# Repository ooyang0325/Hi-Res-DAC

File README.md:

# Hi-Res DAC + balanced headphone amplifier

The current layout review candidate is the editable [120 × 100 mm integrated-audio KiCad board](hardware/DAC_HPA_120x100_INTEGRATED_AUDIO_STUDY_ONLY.kicad_pcb), with manual placement and partial routing, paired with the [schematic](hardware/DAC_HPA.kicad_sch). Parts List v0.9 and Calculation Package v1.1 remain the baseline; the [captured ECO](hardware/FUNCTIONAL_ECO_2026-09-28.md) adds buffered supervisor readbacks and local J702 TVS parts. The incoming layout engineer should start with the [29 September handoff](hardware/LAYOUT_ENGINEER_HANDOFF_2026-09-29.md); peer reviewers can use the [reviewer guide](hardware/REVIEWER_START_HERE.md). The full-rate MCU capture guard, physical overlays, output routability and JLCPCB process gates remain open. No PCB manufacturing or PCBA order files are released.

## GitLab CI/CD

`.gitlab-ci.yml` uses the fixed official KiCad 10.0.1 container. Every pipeline checks schematic regeneration, netlist/ERC, the exact ECO delta, attach-charge arithmetic, placement geometry, JLC fabrication/assembly proxies, DRC and 3D model paths. A successful pipeline delivers the nine-page review PDF, the integrated-audio board's 3D GLB and top/L2/L3/bottom SVGs, earlier board GLBs for comparison, reviewer guides, BOM CSVs and a ZIP of the committed source as downloadable artifacts for 30 days.

The GitLab review package is **not** a manufacturing release. The connector and physical gates are tracked in [connector review](hardware/CONNECTOR_REVIEW.md) and [PCBA process review](hardware/PCBA_PROCESS_REVIEW.md). A routed PCB and CPL would be required for a PCBA upload.

The latest [DAC/core checkpoint](hardware/DAC_CORE_ROUTE_STUDY.md) records BCLK/LRCLK/SDATA at 22.213/22.324/22.879 mm and MCLK at 8.381 mm. The current integrated board has 544 footprints, 250 nets, 855 track/via items (143 vias), 864 full ratsnest links, 499 DRC-unconnected items and zero DRC violations. Its manual delta is 138 moves, eight source-copper removals and 828 additions. C622 has local 3V3D and GND copper; the global 3V3D feed remains open. All 12 U609/U610 timer branches pass the ≤8 mm screen without timer-net vias; C635/C636 U609 bypasses are locally connected, while upstream rail feeds and U609 VT/control escapes remain open. The [integrated-audio route study](hardware/INTEGRATED_AUDIO_ROUTE_STUDY.md) covers the DAC/I/V, amplifier-input, U501 and amplifier-to-jack copper including the completed U609/U610 timer branches and U609 local bypass work. Two U202 and five U301 exposed-pad vias are filled and capped; U401/U402 output-amplifier EP thermal routes remain open. The [via-pad audit](hardware/INTEGRATED_AUDIO_VIA_PAD_PROCESS_AUDIT.json) still flags 45 unfilled via-to-SMT-pad sites within 0.35 mm for JLC mask/process review. Full routing, system ESD, EMI and audio tests remain open; zero DRC violations apply to partial copper only.

The [schematic simplification review](hardware/SCHEMATIC_SIMPLIFICATION_REVIEW.md) lists three small DNF options for later review. Both headphone jacks and USB High mode remain required. The [discharge capture review](hardware/DISCHARGE_CAPTURE_REVIEW.md) identifies an open U303 calculation mismatch and links a separate [three-resistor 2512 fit option](hardware/DAC_HPA_120x100_DISCHARGE_FIT_OPTION_ONLY.kicad_pcb); the captured EN connection remains intentional, and the option is not a schematic/BOM change. The [Freerouting probe](hardware/FREEROUTING_PROBE.md) rejected a whole-board route and records two individually reviewed low-speed paths adopted later. The [functional-ECO board](hardware/DAC_HPA_120x100_FUNCTIONAL_ECO_STUDY_ONLY.kicad_pcb) is the preceding placement baseline; the former primary and [macro study](hardware/MACRO_PLACEMENT_REVIEW.md) are earlier comparisons. No PCBA order is authorized.

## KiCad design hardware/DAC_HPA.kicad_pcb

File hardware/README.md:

# DAC-HPA KiCad schematic and routing studies

**Sending this design for peer review?** Begin with the [layout handover report](LAYOUT_HANDOVER_REPORT.md) and [REVIEWER_START_HERE.md](REVIEWER_START_HERE.md), then use the [schematic](SCHEMATIC_REVIEW_GUIDE.md), [placement](PLACEMENT_REVIEW_GUIDE.md), and [command-line visual inspection](PCB_CLI_VISUAL_REVIEW.md) guides. The [findings template](REVIEW_FINDINGS_TEMPLATE.md) records actionable review results against one Git commit.

The [functional-ECO placement baseline](DAC_HPA_120x100_FUNCTIONAL_ECO_STUDY_ONLY.kicad_pcb) is a separate 120 × 100 mm review board made from explicit hand-selected coordinates. It includes the [readback, J702 TVS and I/V A/B-channel schematic ECO](FUNCTIONAL_ECO_2026-09-28.md), a tighter DAC bypass row and the local J702 TVS branches. The [integrated audio study](INTEGRATED_AUDIO_ROUTE_STUDY.md) is the current routing review candidate; the newer [DAC/core checkpoint](DAC_CORE_ROUTE_STUDY.md) records its latest clock, I²S and local power routes. The [Freerouting probe](FREEROUTING_PROBE.md) rejects the whole-board result and documents two selectively adopted low-speed routes. [Layout review](FUNCTIONAL_ECO_LAYOUT_REVIEW.md) and [constraint disposition](CONSTRAINT_DISPOSITION_V2.md) state the remaining route work. `DAC_HPA.kicad_pcb` and the [prior macro study](MACRO_PLACEMENT_REVIEW.md) are historical comparisons; they predate the eight added parts.

Open `DAC_HPA.kicad_pro` or `DAC_HPA.kicad_sch` in KiCad 10. The root page links eight circuit sheets following Design Spec v1.1, Schematic Design Notes v1.0, Parts List v0.9, and Capture Update Note v1.0.

`DAC_HPA_review_only.pdf` is a nine-page visual export of the current provisional capture. The expanded protection sheet uses A1; smaller blocks use A2/A3/A4. Each sheet title block identifies v1.1-ECO1 and the open F01/F03/G-1–G-4 holds. The KiCad project is the editable source.

## Current status

- The v0.9 workbook has 526 netlisted designators and 1,445 pin rows; those rows still match Calculation Package v1.1. The [asserted functional ECO](FUNCTIONAL_ECO_2026-09-28.md) adds eight parts and reassigns equivalent U403/U404 A/B channels to match the manual I/V macro. KiCad now has **534 netlisted designators, 1,465 pins, 1,422 connected pins, 43 no-connect pins and 250 named nets**, plus four grounded mounting holes and seven fiducials. The exact **34** workbook-to-capture pin/net differences are checked; they include the earlier D705/D706 polarity fix. J702 pins 5/6 remain no-connect break contacts.
- Per-part MPN, LCSC code, fit class, package, and rating/tolerance properties are included for later [JLCPCB BOM preparation](https://jlcpcb.com/help/article/how-to-generate-the-bom-and-centroid-file-from-kicad). The owner approved changing U403/U404 from workbook OPA2210IDR SOIC-8 to OPA2210IDGKR VSSOP-8, C2876414. `generate_schematic.py` asserts the old workbook entry and applies this explicit override; `IV_7MM_RECHECK.md` records the provisional 7 mm input-route reassessment and sourcing/footprint limitations.
- The review-only JLCPCB BOM contains **463 placed parts**, seven owner-fitted and nine DNF parts. Fourteen placed parts have no LCSC code and need the documented global-sourcing process. The three CSVs are **not** an order package; a routed PCB and CPL are still required.
- The schematic-aligned four-layer **120 × 100 mm functional-ECO baseline** has **544 footprints and 250 named nets**; J703 remains a schematic DNF option with no PCB pads. Its partial copper comprises J701/J702 local TVS branches and the hand-routed X201→R203→U301 MCLK trunk, R227 return and R665→U607 monitor input: **28 F.Cu tracks, seven vias** and one filled L2 GND zone. It has zero geometry DRC violations and 1,144 full ratsnest gaps. The old 536-footprint primary and 100 × 80/100 × 100 mm boards are historical comparisons.
- The [separate 270° output-macro study](OUTPUT_MACRO_ROUTE_STUDY.md) keeps the same schematic/pad map and manually connects all four U401/U402 amplifier outputs and local feedback to K601–K604 relay inputs. Its partial copper passes custom-rule DRC, but the jack outputs, input/T networks, supply returns and L3/L4 audio return remain on hold; it is a comparison, not the primary order board.
- The current [integrated-audio routing study](INTEGRATED_AUDIO_ROUTE_STUDY.md) routes four DAC→I/V inputs, eight I/V→first-T feeds, all eight local input T triplets and all four amplifier-to-jack paths. The current board has **855 track/via items (143 vias), zero DRC violations, 499 DRC-reported unconnected items and 864 full `pcbnew` ratsnest links**. Its manual record has **138 footprint moves, eight removed source-copper items and 828 added items**. DACL/DACLB/DACR/DACRB no-via F.Cu routes measure **4.294/6.030/6.837/4.786 mm** against the provisional 7 mm target, leaving DACR **0.163 mm**. Saved L2 GND is directly below all four input traces at 0.01 mm route samples and offsets 0, ±0.05, ±0.10 mm. The longest I/V→first-T feed is **47.752 mm** on the right; the largest projected 2D I/V feedback area is **4.875 mm²**, excluding vertical and return-current area. DACL's U403→C417 feedback branch still lacks direct L2 for **1.9426 mm** of centreline (**+0.0597 mm** from the like-for-like committed baseline). Central VREF copper reaches **14.422 mm**. Extract summing-node capacitance, the DACL feedback return, 3D loop geometry, right-side cross-layer coupling and VREF noise before I/V sign-off.
- The newer [DAC/core checkpoint](DAC_CORE_ROUTE_STUDY.md) records U202 local bypass routes at 1.103/2.056/3.057 mm, U302 VIN→C301 at 0.875 mm and OUT→C302 at 2.131 mm, and connected U303→DAC 1V3 copper at **25.393 mm with two vias**. C622 at **(108.65, 105.50)** has a **4.615 mm** U604.8→C622.1 path and a **1.020 mm** C622.2→Ø0.7/0.3 mm GND via path at **(110.15, 105.50)**, with saved L2 GND beneath both; the global 3V3D feed remains open. Thirty-five local GND pads reach L2. Two U202 and five U301 EP vias are filled/capped; U401/U402 output-amplifier EP thermal routes remain open. The via-pad audit reports zero unfilled overlaps and zero unfilled gaps below 0.10 mm; **45** unfilled via-to-SMT-pad sites within 0.35 mm need JLC mask/process review. Local film/via/timer geometry gates pass, while those 45 process reviews remain open.
- The integrated checkpoint routes all 12 U609/U610 timer branches under the named-pad ≤8 mm screen without timer-net vias. U609 LP C/Q/R routes are **6.089/5.340/4.943 mm** and LN routes **6.038/5.814/6.685 mm**; U610 LP routes are **6.442/7.607/1.789 mm** and LN routes **7.177/7.712/7.787 mm**. C631/C632/C633/C634 GND returns reach L2 in **3.580/3.656/2.650/2.650 mm**. C635/C636 U609 VPOS/VNEG bypasses connect with 11 new vias (six GND, three VPOS, two VNEG). Upstream rail feeds and U609 VT/control escapes remain open. U605/R675/R676/R679/R677 moved left 1.2 mm and C625 moved beside R666, clearing six measured 5 mm I²S/protection gaps. C638 uses a two-via L3 VNEG bridge to keep the timer paths clear. C636 has a pair-specific **0.60 mm** side-courtyard gap to C631/C632; all four film-cap north/south solder approaches pass at ≥**1.5 mm** (minimum **3.045 mm**) per the [film solder-access audit](INTEGRATED_AUDIO_FILM_SOLDER_ACCESS_AUDIT.json).
- The [schematic simplification review](SCHEMATIC_SIMPLIFICATION_REVIEW.md) lists three small DNF options for later decision. The owner keeps both headphone jacks and USB High mode; no populated output links, relays, protection or hold-up parts are proposed for deletion.
- The [discharge capture review](DISCHARGE_CAPTURE_REVIEW.md) keeps the intended U303 EN=3V3D connection and identifies stale C06/C12 assumptions. A separate [physical fit option](DAC_HPA_120x100_DISCHARGE_FIT_OPTION_ONLY.kicad_pcb) tries three provisional 2512 discharge-resistor bodies. Its [audit](DISCHARGE_FIT_OPTION_SUMMARY.json) passes nominal body-edge, overlap, 3D and DRC screens, but it is not schematic/BOM aligned or a release board; maker/JLC lands, source feeds, thermal behavior and shutdown timing remain open.
- The [29 September layout-engineer handoff](LAYOUT_ENGINEER_HANDOFF_2026-09-29.md) identifies the primary board, CLI inspection sequence, route status, the separate discharge fit option and the next engineer's release gates.
- U501 local switching, VIN, VPOS/VNEG cap and feedback groups now have copper. Three bounded **0.20 mm** WSON VIN escapes precede the wider `5V_ANA_F` feeder. Its B.Cu feeder now detours around F.Cu `N5_FBP`: projected track overlap **0.1663→0 mm²** and unshielded pad-inclusive projection **0.0861→0 mm²**. The original via antipad remains; VIN3→C507 is **6.014 mm** within its 6.1 mm bound. C510/C511 GND vias are **8.160/6.767 mm** from U501's GND via by straight L2 via spacing, not an extracted return path. The board has zero exact or near-90° bends, zero footprint bbox overlaps, and zero classified JLC spacing findings. Full routing, system ESD, EMI/audio tests, measured R-15 and F01–F04/G-3/G-4 remain on HOLD. Courtyard gaps near C423/C426 are **0.150–0.194 mm**; C437/J701/K602 and via mask also need JLC order DFM review.
- Both U401/U402 pin-8 EN inputs have copper to the shared local VPOS bypass network. A custom rule screens 2 mm F.Cu left/right separation before the output links. With the [review-only 1 mΩ-max output-link candidate](OUTPUT_LINK_BOM_ECO.md), conditional worst 4.4 mm estimates are 0.3862/0.3737 Ω (L/R) at 1 kHz and 0.3990/0.3864 Ω in the 20 kHz model sensitivity. Contact/via assumptions, measured R-15 and physical/JLC gates still hold fabrication release.
- Every current footprint/pad net matches the ECO schematic. The new DAC high-frequency capacitors are 1.86–2.30 mm by pad distance from their supply pins; the U621 high-impedance input stubs are 1.69/1.86 mm by pad distance. The J702 TVS signal branches are 3.861/3.250 mm. The custom J701/J702 enlarged slot lands retain ≥0.31 mm worst calculated copper ring under the stated JLC slot tolerance. Physical G-3 overlays and JLC DFM remain open.
- All **478 component bodies** on the current candidate have resolvable 3D models; 66 test/debug/mechanical copper items intentionally have none. `3D_MODEL_REVIEW.md` distinguishes exact JLC/Toshiba sources from approximate oscillator and film-capacitor bodies. Open the current candidate in **View → 3D Viewer**.
- `verify_critical_footprints.py` checks 56 critical pad dimensions, pad types and hole/paste properties, including U202's exposed pad, the new TI DGK and onsemi SOT-23 lands, and J101/J701/J702 slots and locating holes. Physical G-3 overlays are still open.
- `G3_CONNECTOR_OVERLAY_REVIEW_ONLY.svg` and `G3_PART_OVERLAY_REVIEW_ONLY.svg` are printable A4 1:1 overlays for 30 unique footprint patterns, including U621 and the J702 TVS package; first measure each 10 mm reference bar. `G3_OVERLAY_INDEX.md` identifies the patterns and `G3_OVERLAY_CHECKLIST.md` holds editable physical sample results. The two-sample DMM and polarity templates are `G1_G2_CONTINUITY_RECORD.md` and `G4_POLARITY_CHECKLIST.md`.
- KiCad ERC reports zero violations. Confirmed power, logic, oscillator and open-collector outputs are typed; most other generated pins remain passive, so ERC does **not** substitute for a datasheet-level electrical review.
- `verify_design_notes.py` checks 1,002 selected circuit and approved-correction assertions. `SOURCE_RECONCILIATION.md` and the [ECO note](FUNCTIONAL_ECO_2026-09-28.md) record controlled changes from the source set.
- The v1.1 design documents mark schematic capture and provisional placement GO and originally hold routing until G-1–G-4 pass. The owner reports both J101 samples match the USB-C map, both J701 samples match the intended audio and 9/10 switch maps, and both J702 samples match the TRS and break map. On 27 September 2026 the owner waived the G-1/G-2 raw measurement log; these reported results are accepted for layout planning without independent evidence. G-3 overlays and G-4 polarity still hold routing, as do the new routability and audio/EMI placement conflicts. J702 supports TRS plugs only. `PRELAYOUT_GATES.md` tracks the gate evidence and later G-5/G-6 holds. See `CONNECTOR_REVIEW.md` for connector maps and copper-ring decision, `POLARITY_REVIEW.md` for the D705/D706 correction, and `CAD_models_to_upload.md` for exact 3D models still desired.
- `PCBA_PROCESS_REVIEW.md` records the J101/J702 plated slots with no paste apertures and the exact JLCPCB process question to resolve before assembly release. The v1.1 calculation package's starting output-impedance estimates are 0.251 Ω (3.5 mm) and 0.383 Ω (4.4 mm), with 50 mΩ budgeted per output link. The candidate link's 1 mΩ maximum reduces that model term; routed copper and illustrative vias give the current conditional 4.4 mm estimates above. The 3.5 mm signal-only lower bounds are 0.2255/0.2188 Ω (L/R), with sleeve return unextracted. Both jacks still need measurement against R-15, and the 50 mΩ per jack-contact estimate has no maker maximum.

The included JLCPCB library data came from LCSC codes through `dsa-t/jlc-kicad-lib-loader` 1.0.11. `JLC_Source/JLC_DAC_HPA.elibz` now keeps **42 source CAD entries**, including exact C507231 for U621; `JLC_Imported.pretty` contains native KiCad footprints, and `jlc_footprints.json` records pad comparisons. The TI DCK example land and JLC C507231 land differ, so U621 remains a G-3 overlay item. The project footprints are in `DAC_HPA.pretty`; custom land sources are in `FOOTPRINT_SOURCES.md`.

## Regenerate and verify

With Python 3, `openpyxl`, and KiCad 10 installed:

```sh
python3 hardware/audit_jlc_library.py
python3 hardware/derive_connector_footprints.py
python3 hardware/generate_schematic.py
python3 hardware/verify_schematic.py
python3 hardware/verify_design_notes.py
python3 hardware/export_assembly_review.py
python3 hardware/check_attach_charge.py
python3 hardware/check_spi2_capture_contract.py
/Applications/KiCad/KiCad.app/Contents/Frameworks/Python.framework/Versions/Current/bin/python3 hardware/verify_critical_footprints.py
/Applications/KiCad/KiCad.app/Contents/Frameworks/Python.framework/Versions/Current/bin/python3 hardware/audit_placement.py hardware/DAC_HPA_120x100_FUNCTIONAL_ECO_STUDY_ONLY.kicad_pcb --height 100 > /tmp/dac-eco-placement.json
/Applications/KiCad/KiCad.app/Contents/Frameworks/Python.framework/Versions/Current/bin/python3 hardware/audit_dfa_dfm.py hardware/DAC_HPA_120x100_FUNCTIONAL_ECO_STUDY_ONLY.kicad_pcb > /tmp/dac-eco-dfa.json
/Applications/KiCad/KiCad.app/Contents/Frameworks/Python.framework/Versions/Current/bin/python3 hardware/audit_jlc_fab.py hardware/DAC_HPA_120x100_FUNCTIONAL_ECO_STUDY_ONLY.kicad_pcb > /tmp/dac-eco-fab.json
/Applications/KiCad/KiCad.app/Contents/MacOS/kicad-cli pcb drc --format json --severity-error --severity-warning -o /tmp/dac-eco-drc.json hardware/DAC_HPA_120x100_FUNCTIONAL_ECO_STUDY_ONLY.kicad_pcb
/Applications/KiCad/KiCad.app/Contents/Frameworks/Python.framework/Versions/Current/bin/python3 hardware/check_functional_eco_layout.py hardware/DAC_HPA_120x100_FUNCTIONAL_ECO_STUDY_ONLY.kicad_pcb /tmp/dac-eco-placement.json /tmp/dac-eco-dfa.json /tmp/dac-eco-fab.json /tmp/dac-eco-drc.json
/Applications/KiCad/KiCad.app/Contents/Frameworks/Python.framework/Versions/Current/bin/python3 hardware/audit_3d_models.py hardware/DAC_HPA_120x100_FUNCTIONAL_ECO_STUDY_ONLY.kicad_pcb
/Applications/KiCad/KiCad.app/Contents/MacOS/kicad-cli sch export pdf -o hardware/DAC_HPA_review_only.pdf hardware/DAC_HPA.kicad_sch
```

`generate_schematic.py` reads `doc/DAC_HPA_Parts_List_v0.9.xlsx`, asserts the source pin maps, applies the ECO and rewrites the generated sheets/symbol library. Run the CAD audits before regeneration when source data changes. Manual KiCad edits to generated schematic files are replaced on regeneration; edit the generator's asserted ECO or make a controlled new workbook revision. `manual_functional_eco_layout.py` records all additional hand-selected positions and local J702 tracks; its UUIDs may differ on reproduction, while `check_functional_eco_layout.py` checks the committed geometry and schematic pad map. `manual_integrated_audio_study.py` replays the frozen manifest of **138 footprint moves, eight source-copper removals and 828 added copper items**; `check_integrated_audio_study.py` compares them with the review board. The command block above verifies the earlier functional-ECO baseline; the [integrated CI job](../.gitlab-ci.yml) audits the current candidate. `place_board.py --force` is only for historical automatic comparisons.

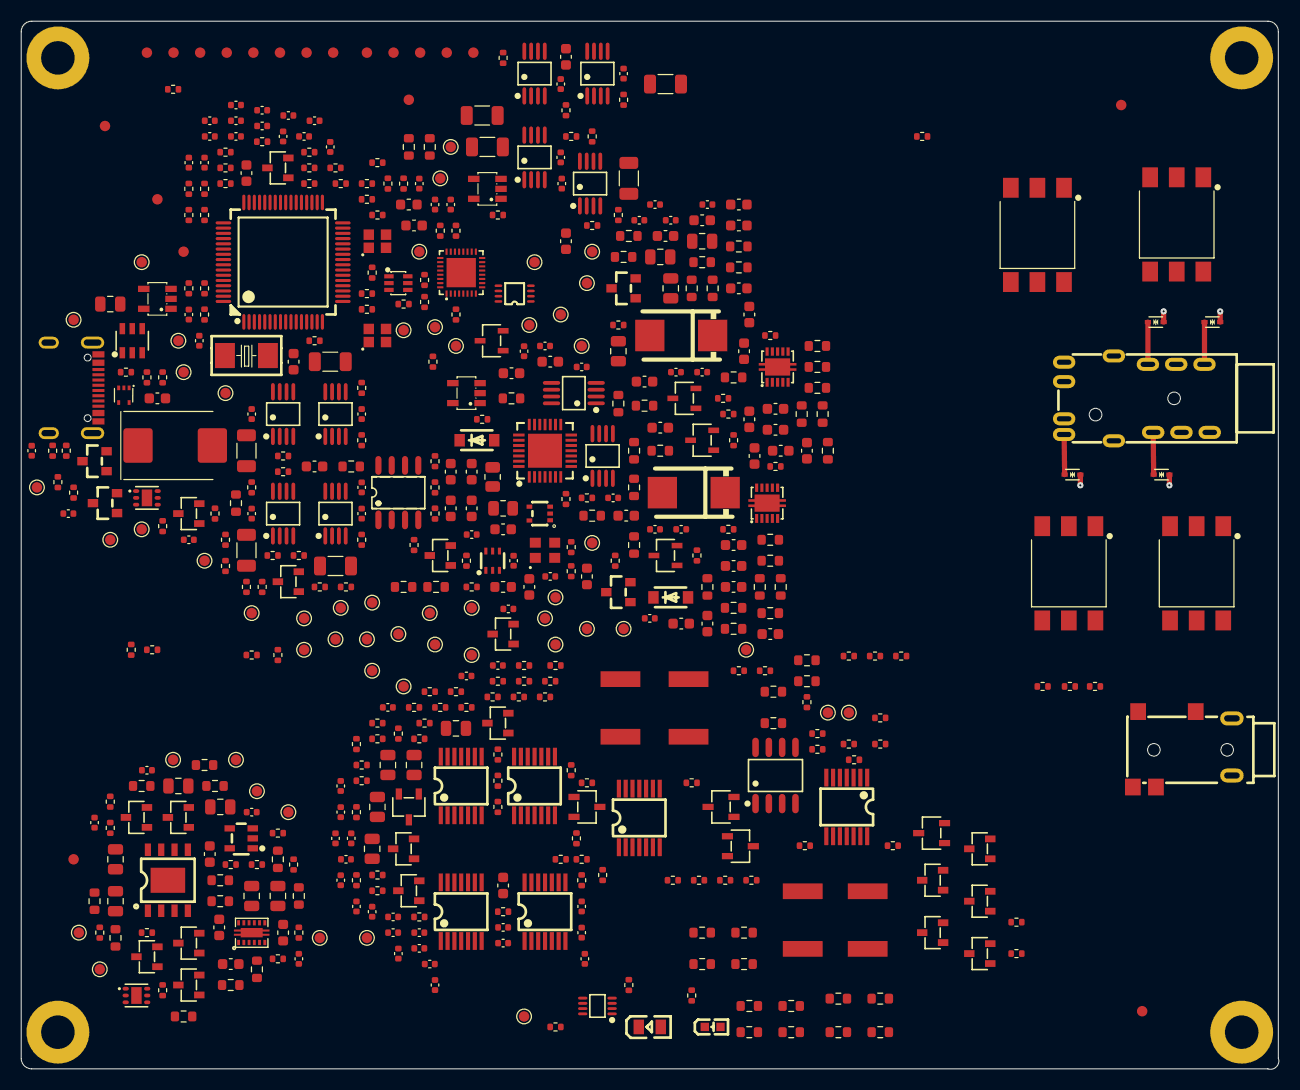
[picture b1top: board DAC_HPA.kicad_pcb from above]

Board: 4 copper layers, 120.0 x 100.0 mm, 536 parts (0 on the bottom side), 245 nets.

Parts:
C101: 4.7 nF; C_0402_1005Metric
C102: 2.2 µF; C_0805_2012Metric
C103, C516, C624: 100 pF; C_0402_1005Metric
C104, C203, C204, C205, C206, C207, C208, C209, C210, C212, C213, C214, C215, C218, C219, C222, C223, C224, C305, C306, C307, C308, C309, C409, C410, C411, C412, C423, C424, C425, C426, C505, C515, C618, C619, C622, C623, C626, C627, C628, C630, C635, C636, C637, C638, C655, C656, C657, C658, C659, C660, C661, C662, C663, C664, C665, C666: 100 nF; C_0402_1005Metric
C201, C202, C421: 33 pF; C_0402_1005Metric
C211: 2.2 µF; C_0402_1005Metric
C217, C514, C620, C621: 10 nF; C_0402_1005Metric
C220, C221, C311, C312, C441, C501, C506, C508, C617: 1 µF; C_0603_1608Metric
C301, C302, C303, C304, C310, C439, C440, C502: 2.2 µF; C_0603_1608Metric
C401, C402, C403, C404, C405, C406, C407, C408: 10 pF; C_0603_1608Metric
C413, C414, C415, C416, C507, C509, C510, C511, C512, C513: 10 µF; C_0805_2012Metric
C417, C418, C419, C420: 820 pF; C_0603_1608Metric
C431, C432, C433, C434, C435, C436, C437, C438: 1.8 nF; C_0603_1608Metric
C442, C443: 220 µF; CASE-D_7343
C608, C609, C610, C611, C616: 4.7 µF; C_0805_2012Metric
C625: 82 pF; C_0402_1005Metric
C629, C639, C640, C641, C642: 1 nF; C_0402_1005Metric
C631, C632, C633, C634: 220 nF; C631_ECHU1H224GX9_D4
C643, C644, C645, C646: 3.3 nF; C_0603_1608Metric
C647, C648, C649, C650, C651, C652, C653, C654: 100 nF; C_1206_3216Metric
D102: 12 V; D102_SMDJ12A_HandSolder
D104, D105: Nexperia BAT54,215; SOT-23_L2.9-W1.3-P1.90-LS2.4-BR
D405, D406, D407, D408: BAT54S; SOT-23-3_L3.0-W1.7-P0.95-LS2.9-BR
D411, D412: PMEG2010AEH; SOD-123F_L2.8-W1.8-LS3.7-RD
D413, D414: BAT54; SOT-23_L2.9-W1.3-P1.90-LS2.4-BR
D609, D610: BAS70-04; SOT-23-3_L2.9-W1.3-P1.90-LS2.4-BR
D701, D702, D703, D704: 5 V; SOD-523_L1.2-W0.8-LS1.6-BI
D705: Green; LED0805-R-RD
D706: Red; LED-SMD_L1.6-W0.8-R-RD
FB202, FB301, FB302: 600 Ω @ 100 MHz; L_0603_1608Metric
FB501: 120 Ω @ 100 MHz; L_0603_1608Metric
FID1, FID2, FID3, FID4, FID5, FID6, FID7: Fiducial; Fiducial_1mm_Mask2mm
J101: GCT USB4105-GF-A; J101_USB4105-GF-A_12lands_4stakes
J201: PCB pads (no component); J201_8_DebugPads_P2.54mm
J202: PCB pads (no component); J202_5_JTAGPads_P2.54mm
J701: G-Switch GT-3321667P-01; J701_GT-3321667P-01_maker_slots
J702: HRO PJ-332A-6A; J702_PJ-332A-6A_peg_holes
K601, K602, K603, K604: TLP3545A; K601_TLP3545A_LF1_HandSolder
MH1, MH2, MH3, MH4: M3 plated to GND; MountingHole_M3_3.2mm_Pad6.0mm
Q207, Q502, Q503, Q504, Q505, Q506, Q616, Q617, Q619, Q620, Q622: AO3400A; SOT-23-3_L2.9-W1.3-P1.90-LS2.4-BR
Q507, Q612, Q614: MMBT3904; SOT-23-3_L2.9-W1.3-P1.90-LS2.4-BR
Q618, Q621: 2N7002; SOT-23-3_L2.9-W1.3-P1.90-LS2.4-BR
Q623, Q624, Q625, Q626, Q627: MMBT3904; SOT-23-3_L2.9-W1.6-P1.90-LS2.8-BR
R101, R102, R628, R629, R630, R631, R639, R663: 5.1 kΩ; R_0402_1005Metric
R103, R104, R201, R202, R207, R208, R212, R213, R216, R217, R218, R227, R231, R232, R234, R236, R238, R239, R305, R508, R522, R951: 10 kΩ; R_0402_1005Metric
R105, R108, R235, R240, R303, R505, R511, R512, R513, R535, R537, R538, R646, R647, R648, R653, R654, R655, R656, R662, R667, R669, R673, R680, R687, R691, R693, R695, R696, R925, R939, R950: 100 kΩ; R_0402_1005Metric
R106, R536: 47 kΩ; R_0402_1005Metric
R107, R241, R417, R418, R419, R420: 0 Ω; R_0402_1005Metric
R109, R532, R688, R689, R935, R936, R937: 470 kΩ; R_0402_1005Metric
R203, R204, R205, R206, R210, R211, R215, R224, R225: 33 Ω; R_0402_1005Metric
R228, R229, R230, R242, R243, R244, R245, R246, R665: 330 Ω; R_0402_1005Metric
R237, R643, R644: 4.7 kΩ; R_0402_1005Metric
R301, R302: 2.2 Ω; R_0805_2012Metric
R401, R403, R405, R407, R409, R411, R413, R415: 1.30 kΩ; R_0603_1608Metric
R402, R404, R406, R408, R410, R412, R414, R416: 2.00 kΩ; R_0603_1608Metric
R423, R424, R425, R426: 698 Ω; R_0603_1608Metric
R431: 9.76 kΩ; R_0603_1608Metric
R432: 10.0 kΩ; R_0603_1608Metric
R438, R439, R440, R441, R442, R443, R444, R445: 680 Ω; R_0603_1608Metric
R446, R447: DNF (237 k … 2 M); R_0603_1608Metric
R501: 221 kΩ; R_0603_1608Metric
R502, R504: 100 kΩ; R_0603_1608Metric
R503: 205 kΩ; R_0603_1608Metric
R509: 4.75 kΩ; R_0603_1608Metric
R510: 3.74 kΩ; R_0603_1608Metric
R526, R528: 22 kΩ; R_0402_1005Metric
R527, R529: 10 Ω; R_0603_1608Metric
R530: 4.7 Ω; R_0603_1608Metric
R531: 1 Ω; R_0603_1608Metric
R533: 15.0 kΩ; R_0603_1608Metric
R534: 11.0 kΩ; R_0603_1608Metric
R624, R625, R626, R627, R658, R661: 6.8 kΩ; R_0402_1005Metric
R632, R633, R634, R635, R640: 16.9 kΩ; R_0402_1005Metric
R641, R642: 24.9 Ω; R_0402_1005Metric
R645, R692, R701, R703: 1 kΩ; R_0402_1005Metric
R657, R659, R670: 10.0 kΩ; R_0402_1005Metric
R660, R690, R694, R916, R917, R918, R919, R926, R927, R928, R929: 330 kΩ; R_0402_1005Metric
R666, R668, R930, R931, R932, R933, R938, R940: 1.00 MΩ; R_0402_1005Metric
R671: 2.2 MΩ; R_0402_1005Metric
R672: 237 kΩ; R_0402_1005Metric
R674, R702: 2.2 kΩ; R_0402_1005Metric
R675, R682: 44.2 kΩ; R_0402_1005Metric
R676, R683: 200 kΩ; R_0402_1005Metric
R677, R684: 300 kΩ; R_0603_1608Metric
R678, R685, R901, R903, R905, R907, R909, R911, R913, R915: 1.00 MΩ; R_0603_1608Metric
R679, R686: 22 MΩ; R_0402_1005Metric
R681: 4.7 MΩ; R_0402_1005Metric
R900, R902, R904, R906, R908, R910, R912, R914: 487 kΩ; R_0603_1608Metric
R920, R921, R922, R923: 110 kΩ; R_0402_1005Metric
R924: 69.8 kΩ; R_0402_1005Metric
R934: 360 kΩ; R_0402_1005Metric
R941: 88.7 kΩ; R_0402_1005Metric
R942, R943, R944, R945, R946, R947, R948, R949: 910 kΩ; R_0402_1005Metric
TP701, TP702, TP703, TP704, TP705, TP706, TP707, TP708, TP709, TP710, TP711, TP712, TP713, TP714, TP715, TP716, TP717, TP718, TP719, TP720, TP721, TP722, TP723, TP724, TP725, TP726, TP727, TP728, TP729, TP730, TP731, TP733, TP734, TP735, TP736, TP737, TP738, TP739, TP740, TP741, TP742, TP743, TP744, TP745, TP746, TP747, TP748, TP749, TP750, TP751, TP752, TP753: No part; TestPad_D1.0mm
TP732: PCB pads (no component); TestPad_D1.0mm
U101: ST USBLC6-2SC6; SOT-23-6_L2.9-W1.6-P0.95-LS2.8-BL
U102: TI TPS25200DRVR; WSON-6_L2.0-W2.0-P0.65-TL-EP_PAD
U103: TI TPD2E2U06DRLR; SOT-553-5_L1.6-W1.2-P0.50-LS1.6-TL-1
U201: CH32V307RCT6; LQFP-64_L10.0-W10.0-P0.50-LS12.0-BL
U202: AGRV2KQ32; QFN-32_L4.0-W4.0-P0.40-BL-EP2.7_EP
U205: 74LVC1G157; SOT-363_L2.0-W1.3-P0.65-LS2.1-BR
U206: 74LVC1G11; SC-88-6_L2.0-W1.3-P0.65-LS2.1-BL
U208: 74LVC3G34; VSSOP-8_L2.1-W2.4-P0.50-LS3.2-BR
U301: ES9018K2M; QFN-28_L5.0-W5.0-P0.50-BL-EP3.3_EP
U302: 3.3 V, 250 mA; SOT-23-5_L3.0-W1.7-P0.95-LS2.8-BR
U303: 1.300 V (R533/R534); SOT-23-5_L3.0-W1.7-P0.95-LS2.8-BR
U401, U402: OPA1622IDRCR; VSON-10_L3.0-W3.0-P0.50-BL-EP1.65_PAD
U403, U404: OPA2210IDGKR; VSSOP-8_L3.0-W3.0-P0.65-LS5.0-BL
U501: +3.85 / -3.72 V; WSON-12_L3.0-W2.0-P0.50-BL-EP_PAD
U502: 3.3 V, 150 mA; SOT-23-5_L3.0-W1.7-P0.95-LS2.8-BR
U503: TI TPS259621DDAR; ESOP-8_L4.9-W3.9-P1.27-LS6.0-BL-EP_PAD
U504: 3.3 V, 1 A; WSON-6_L2.0-W2.0-P0.65-TL-EP_PAD
U505: TI TMUX1101DBVR; SOT-23-5_L2.9-W1.6-P0.95-LS2.8-BR
U603, U606, U609, U610, U611, U612: TLV1704; TSSOP-14_L5.0-W4.4-P0.65-LS6.4-BL
U604: OPA2333; SOP-8_L4.9-W3.9-P1.27-LS6.0-BL
U605: TLV3402; SOIC-8_L4.9-W3.9-P1.27-LS6.0-BL
U607: 74AUP1G17; TSSOP-5_L2.1-W1.3-P0.65-LS2.2-BR
U608: 74LVC1G74; VSSOP-8_L2.3-W2.0-P0.50-LS3.1-BR
U613, U614, U615, U616, U617, U618, U619, U620: TLV3402; VSSOP-8_L3.0-W3.0-P0.65-LS5.0-BL
X201: 80.000 MHz; X201_KC2520K80_Kyocera
X202: 49.152 MHz; X202_X203_NDK_NZ2520SDA
X203: 45.1584 MHz; X202_X203_NDK_NZ2520SDA
Y201: 8 MHz; CRYSTAL-SMD_L5.0-W3.2

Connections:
1V3: C309.1, C310.1, C312.1, R530.1, R533.1, R670.1, TP706.1, U301.21, U303.5
3V3A: C302.1, C441.1, D104.1, FB302.1, R301.1, R302.1, R431.1, R446.1, R527.1, R628.2, R629.2, R630.2, R631.2, R639.2, R657.1, R675.1, R682.1, R934.1, R938.1, TP705.1, U302.5
3V3D: C217.1, C218.1, C219.1, C222.1, C223.1, C224.1, C311.1, C512.1, C622.1, C623.1, C630.1, FB202.1, FB301.1, J202.1, R207.2, R208.2, R529.1, R690.1, R691.1, TP704.1, U205.5, U206.5, U208.8, U303.1, U303.3, U504.1, U504.2, U604.8, U607.5, U608.7, U608.8, X201.4, X202.4, X203.4
3V3M: C203.1, C204.1, C205.1, C206.1, C207.1, C208.1, C209.1, C210.1, C211.1, C221.1, C502.1, C515.1, C628.1, R201.2, R240.2, R241.1, R512.2, R526.1, R528.1, R648.2, R677.1, R680.1, R684.1, R687.1, TP703.1, U101.5, U201.1, U201.13, U201.19, U201.32, U201.48, U201.64, U502.5, U505.5, U605.8
5V_ANA: C506.1, D105.1, FB501.1, TP702.1, U503.5
5V_ANA_F: C507.1, FB501.2, R505.2, R531.1, R535.1, U501.3, U501.8, U501.12
5V_SYS: C301.1, C501.1, C505.1, D104.3, D105.3, K601.1, K603.1, R105.1, TP701.1, U102.1, U302.1, U503.4, U504.6
ANA_EN: R513.1, TP737.1, U201.53, U503.3
ANA_FAULT_N: R512.1, TP723.1, U201.57, U503.6
ANA_SENSE: C516.1, R535.2, R536.1, TP752.1, U201.14
AUD_EN: Q504.1, Q620.3, R237.2, R508.1, TP738.1, U504.4
AVCC_EN: Q502.1, R236.1, R303.1, TP720.1, U201.52, U302.3
AVCC_L: C303.1, C305.1, D405.2, D406.2, R301.2, TP710.1, U301.15
AVCC_R: C304.1, C306.1, D407.2, D408.2, R302.2, U301.16
BCLK: R204.2, TP715.1, U301.27
BOOT0: J201.6, R202.1, U201.60
CC1: J101.A5, R101.1, R103.1, TP726.1, U103.3
CC1_ADC: R103.2, U201.16
CC2: J101.B5, R102.1, R104.1, TP727.1, U103.5
CC2_ADC: R104.2, U201.17
CPLD_IRQ: U201.39, U202.14
CPLD_JTCK: J202.2, R239.1, U202.25
CPLD_JTMS: J202.3, R238.1, U202.24
CPLD_NRST: J202.4, R231.1, U201.25, U202.4
DACL: C417.1, R423.1, U301.13, U403.2
DACLB: C418.1, R424.1, U301.14, U403.6
DACR: C419.1, R425.1, U301.9, U404.2
DACRB: C420.1, R426.1, U301.10, U404.6
DAC_LOCK: U201.40, U301.23
DAC_RESETB: Q207.3, R305.1, TP746.1, U301.28
DC_PERMIT_N: Q618.3, R648.1, TP722.1, U201.55
DC_SENSE_LN: C609.1, R243.1, R625.2, R629.1, R633.1
DC_SENSE_LP: C608.1, R242.1, R624.2, R628.1, R632.1
DC_SENSE_RN: C611.1, R245.1, R627.2, R631.1, R635.1
DC_SENSE_RP: C610.1, R244.1, R626.2, R630.1, R634.1
DVCC: C308.1, C439.1, FB301.2, R305.2, U301.18
FAM_CLK: R215.2, TP712.1, U202.1
GND: C101.2, C102.2, C103.2, C104.2, C201.2, C202.2, C203.2, C204.2, C205.2, C206.2, C207.2, C208.2, C209.2, C210.2, C211.2, C212.2, C213.2, C214.2, C215.2, C217.2, C218.2, C219.2, C220.2, C221.2, C222.2, C223.2, C224.2, C301.2, C302.2, C303.2, C304.2, C305.2, C306.2, C307.2, C308.2, C309.2, C310.2, C311.2, C312.2, C402.2, C404.2, C406.2, C408.2, C409.2, C410.2, C411.2, C412.2, C413.2, C414.2, C415.2, C416.2, C421.2, C423.2, C424.2, C425.2, C426.2, C431.2, C432.2, C433.2, C434.2, C435.2, C436.2, C437.2, C438.2, C439.2, C440.2, C441.2, C442.2, C443.1, C501.2, C502.2, C505.2, C506.2, C507.2, C509.2, C510.2, C511.2, C512.2, C513.2, C514.2, C515.2, C516.2, C608.2, C609.2, C610.2, C611.2, C616.2, C617.2, C618.2, C619.2, C620.2, C621.2, C622.2, C623.2, C625.2, C626.2, C627.2, C628.2, C629.2, C630.2, C631.2, C632.2, C633.2, C634.2, C635.2, C636.2, C637.2, C638.2, C639.2, C640.2, C641.2, C642.2, C643.2, C644.2, C645.2, C646.2, C647.2, C648.2, C649.2, C650.2, C651.2, C652.2, C653.2, C654.2, C655.2, C656.2, C657.2, C658.2, D102.2, D405.1, D406.1, D407.1, D408.1, D413.1, D414.3, D609.1, D701.2, D702.2, D703.2, D704.2, D705.2, D706.2, J101.A1/B12, J101.B1/A12, J201.5, J202.5, J701.1, J702.1, J702.2, MH1.1, MH2.1, MH3.1, MH4.1, Q207.2, Q502.2, Q503.2, Q504.2, Q505.2, Q506.2, Q507.2, Q618.2, Q619.2, Q620.2, Q621.2, Q622.2, Q623.2, Q624.2, Q625.2, Q626.2, Q627.2, R101.2, R102.2, R106.2, R107.2, R108.2, R202.2, R212.2, R213.2, R216.2, R217.2, R218.2, R227.2, R232.2, R234.2, R235.2, R239.2, R303.2, R404.2, R408.2, R412.2, R416.2, R432.2, R447.2, R502.2, R504.2, R508.2, R509.2, R511.2, R513.2, R532.2, R534.2, R536.2, R538.2, R632.2, R633.2, R634.2, R635.2, R640.2, R646.2, R659.2, R661.2, R663.2, R666.2, R669.2, R673.2, R676.2, R678.2, R683.2, R685.2, R694.2, R696.2, R901.2, R907.2, R909.2, R915.2, R925.2, R935.2, R939.2, R941.2, TP728.1, TP729.1, TP730.1, TP731.1, TP741.1, TP742.1, U101.2, U102.5, U102.PAD, U103.4, U201.12, U201.18, U201.31, U201.47, U201.63, U202.17, U202.30, U202.EP, U205.2, U206.2, U208.4, U301.1, U301.2, U301.5, U301.8, U301.11, U301.12, U301.19, U301.20, U301.22, U301.EP, U302.2, U303.2, U401.3, U402.3, U501.4, U501.PAD, U502.2, U503.1, U503.PAD, U504.3, U504.5, U504.PAD, U505.2, U505.3, U604.4, U605.4, U607.3, U608.4, U613.5, U614.5, U615.5, U616.5, U617.5, U618.5, U619.5, U620.5, X201.2, X202.2, X203.2
I2C_SCL: R207.1, U201.29, U301.3
I2C_SDA: R208.1, U201.30, U301.4
ILIM_HI: R511.1, TP739.1, U201.50, U505.4
JACK_LN: D703.1, J701.6, K602.6
JACK_LP: D701.1, J701.7, J701.8, J702.4, K601.6
JACK_RN: D704.1, J701.2, J701.3, K604.6
JACK_RP: D702.1, J701.4, J701.5, J702.3, K603.6
LED_G: R701.1, U201.37
LED_R: R702.1, U201.38
LEG_LN: K602.4, R418.2, R625.1, R902.1, R906.1, R927.1, R931.1
LEG_LP: K601.4, R417.2, R624.1, R900.1, R904.1, R926.1, R930.1
LEG_RN: K604.4, R420.2, R627.1, R910.1, R914.1, R929.1, R933.1
LEG_RP: K603.4, R419.2, R626.1, R908.1, R912.1, R928.1, R932.1
LINK_FRAME: U202.11, U208.2
LINK_MISO: U201.22, U202.12
LINK_MOSI: U202.10, U208.5
LINK_SCK: U202.9, U208.7
LRCLK: R205.2, TP716.1, U301.26
LRCLK_FB: U201.54, U202.13
MCLK: R203.2, R665.1, R703.1, TP711.1, U301.7
MCLK_EN: R218.1, TP740.1, U202.21, U206.1
N1_SHIELD: C101.1, J101.S1, J101.S2, J101.S3, J101.S4, R107.1
N1_U102_EN: C104.1, Q507.3, R109.2, U102.4
N1_U102_ILIM: R108.1, U102.2
N2_AUD_EN_MCU: R237.1, U201.51
N2_AVCC_EN_G: Q619.3, R236.2, TP719.1, U206.3
N2_BCLK_SRC: R204.1, R228.1, U202.18
N2_BOOT1: R232.1, U201.28
N2_CAP_CK: R228.2, U201.34
N2_CAP_SD: R230.2, U201.36
N2_CAP_WS: R229.2, U201.33
N2_DCS_LN_PIN: R243.2, U201.9
N2_DCS_LP_PIN: R242.2, U201.8
N2_DCS_RN_PIN: R245.2, U201.11
N2_DCS_RP_PIN: R244.2, U201.10
N2_HSE_IN: C201.1, U201.5, Y201.1
N2_HSE_OUT: C202.1, U201.6, Y201.2
N2_J201_3V3: J201.1, R241.2
N2_LINK_FRAME_MCU: U201.20, U208.6
N2_LINK_MOSI_BUF: R225.2, U208.3
N2_LINK_MOSI_MCU: R225.1, U201.23
N2_LINK_SCK_BUF: R224.2, U208.1
N2_LINK_SCK_MCU: R224.1, U201.21
N2_LRCLK_SRC: R205.1, R229.1, U202.19
N2_MCLK_OE: R235.1, R645.1, TP735.1, U201.27, U206.4, X201.1
N2_MCLK_PERMIT: R234.1, U201.35, U206.6
N2_MUX_I0: R210.2, R216.1, U205.3
N2_MUX_I1: R211.2, R217.1, U205.1
N2_MUX_Y: R215.1, U205.4
N2_RESET_DRV: Q207.1, R240.1, U201.41
N2_SDATA_SRC: R206.1, R230.1, U202.20
N2_V3A_MON_PIN: R246.2, U201.24
N2_V33_CPLD: C213.1, C214.1, C215.1, C220.1, FB202.2, R231.2, R238.2, U202.6, U202.16, U202.32
N2_X201_OUT: R203.1, R227.1, X201.3
N2_X202_OUT: R210.1, X202.3
N2_X203_OUT: R211.1, X203.3
N3_1V3_FB: R533.2, R534.1, U303.4
N4_IVL_N: C418.2, D406.3, R403.1, R405.1, R424.2, R654.1, U403.7
N4_IVL_P: C417.2, D405.3, R401.1, R407.1, R423.2, R653.1, U403.1
N4_IVR_N: C420.2, D408.3, R411.1, R413.1, R426.2, R656.1, U404.7
N4_IVR_P: C419.2, D407.3, R409.1, R415.1, R425.2, R655.1, U404.1
N4_LN_INN: C403.1, R406.1, R440.2, U401.6
N4_LN_INP: C404.1, R408.1, R441.2, U401.5
N4_LN_OUT: C403.2, R406.2, R418.1, U401.7
N4_LN_TN: C433.1, R405.2, R440.1
N4_LN_TP: C434.1, R407.2, R441.1
N4_LP_INN: C401.1, R402.1, R438.2, U401.10
N4_LP_INP: C402.1, R404.1, R439.2, U401.1
N4_LP_OUT: C401.2, R402.2, R417.1, U401.9
N4_LP_TN: C431.1, R401.2, R438.1
N4_LP_TP: C432.1, R403.2, R439.1
N4_RN_INN: C407.1, R414.1, R444.2, U402.6
N4_RN_INP: C408.1, R416.1, R445.2, U402.5
N4_RN_OUT: C407.2, R414.2, R420.1, U402.7
N4_RN_TN: C437.1, R413.2, R444.1
N4_RN_TP: C438.1, R415.2, R445.1
N4_RP_INN: C405.1, R410.1, R442.2, U402.10
N4_RP_INP: C406.1, R412.1, R443.2, U402.1
N4_RP_OUT: C405.2, R410.2, R419.1, U402.9
N4_RP_TN: C435.1, R409.2, R442.1
N4_RP_TP: C436.1, R411.2, R443.1
N4_VNEG_IV: C424.1, C426.1, C443.2, D412.2, D414.1, TP751.1, U403.4, U404.4
N4_VPOS_IV: C423.1, C425.1, C442.1, D411.1, D413.3, TP750.1, U403.8, U404.8
N5_C1N: C508.2, U501.9
N5_C1P: C508.1, U501.10
N5_CP: C509.1, U501.5
N5_DAMP: C513.1, R531.2
N5_DIS_13_R: Q506.3, R530.2
N5_DIS_A: Q502.3, Q503.1, R526.2
N5_DIS_A_R: Q503.3, R527.2
N5_DIS_D: Q504.3, Q505.1, Q506.1, R528.2
N5_DIS_D_R: Q505.3, R529.2
N5_DVDT: C514.1, U503.2
N5_FBN: R503.2, R504.1, U501.7
N5_FBP: R501.2, R502.1, U501.2
N5_ILIM: R509.1, R510.1, U503.7
N5_ILIM_HI: R510.2, U505.1
N5_PGOOD: R505.1, R522.1, U501.1
N5_Q507_B: Q507.1, R537.2, R538.1
N5_U102_OFF: R537.1, U201.3
N6_ARM: R692.1, R695.1, U608.5
N6_ARMG: Q622.1, R692.2, R696.1
N6_ARM_MCU: R695.2, U201.26
N6_BL: Q612.1, R643.2
N6_BR: Q614.1, R644.2
N6_CLR_N: Q621.3, R691.2, U608.2, U608.6
N6_CML: C620.1, R653.2, R654.2, TP733.1, U603.4, U603.7
N6_CMR: C621.1, R655.2, R656.2, TP734.1, U603.8, U603.11
N6_CMTH_HI: R657.2, R658.1, U603.5, U603.9
N6_CMTH_LO: R658.2, R659.1, R660.2, U603.6, U603.10
N6_DA_L: R900.2, R901.1, U609.4
N6_DA_R: R908.2, R909.1, U610.4
N6_DB_L: R902.2, R903.1, U609.5
N6_DB_R: R910.2, R911.1, U610.5
N6_DC_L: R904.2, R905.1, U609.7
N6_DC_R: R912.2, R913.1, U610.7
N6_DD_L: R906.2, R907.1, U609.6
N6_DD_R: R914.2, R915.1, U610.6
N6_EL: Q612.2, R641.1, TP743.1, U604.2
N6_EM: Q616.3, R641.2, R642.2, TP745.1
N6_ER: Q614.2, R642.1, TP744.1, U604.6
N6_GMC: Q616.1, R645.2
N6_H: C617.1, Q617.1, Q618.1, R647.2, R671.1, TP724.1, U603.1, U603.2, U603.13, U603.14, U606.1, U606.2, U606.10, U606.14, U609.13, U609.14, U610.13, U610.14
N6_HREF: R693.2, R694.1, U606.11
N6_IREF: R662.2, R663.1, U604.3, U604.5
N6_LWLN: C644.1, R931.2, U615.3, U616.2
N6_LWLP: C643.1, R930.2, U613.3, U614.2
N6_LWRN: C646.1, R933.2, U619.3, U620.2
N6_LWRP: C645.1, R932.2, U617.3, U618.2
N6_M2: Q616.2, Q617.3
N6_M3: Q617.2, Q622.3
N6_MCK_BUF: C624.1, U607.4
N6_MCK_CMP: R667.2, U606.7
N6_MCK_IN: R665.2, U607.2
N6_MCK_RC: C625.1, D609.2, R666.1, R667.1, TP747.1
N6_OAL: R643.1, U604.1
N6_OAR: R644.1, U604.7
N6_OLN_L: Q624.1, R917.2, U609.1, U611.1, U611.14, U614.7, U615.7
N6_OLN_R: Q626.1, R919.2, U610.1, U612.1, U612.14, U618.7, U619.7
N6_OLP_L: Q623.1, R916.2, U609.2, U611.2, U611.13, U613.7, U616.7
N6_OLP_R: Q625.1, R918.2, U610.2, U612.2, U612.13, U617.7, U620.7
N6_ORLN: C640.1, R927.2, U611.8, U611.11
N6_ORLP: C639.1, R926.2, U611.4, U611.7
N6_ORQC: Q627.3, R951.2
N6_ORRN: C642.1, R929.2, U612.8, U612.11
N6_ORRP: C641.1, R928.2, U612.4, U612.7
N6_ORTB: Q627.1, R950.2
N6_ORTEST: R937.2, R950.1, U201.4
N6_PMP: C624.2, D609.3
N6_REF13: R672.2, R673.1, U606.4, U606.9
N6_REFMCK: R668.2, R669.1, U606.6
N6_SL_A: K601.2, K602.1
N6_SL_C: K602.2, Q612.3
N6_SR_A: K603.2, K604.1
N6_SR_C: K604.2, Q614.3
N6_TLN_L: C632.1, Q624.3, R921.2, U609.10
N6_TLN_R: C634.1, Q626.3, R923.2, U610.10
N6_TLP_L: C631.1, Q623.3, R920.2, U609.8
N6_TLP_R: C633.1, Q625.3, R922.2, U610.8
N6_TRIP: Q621.1, R690.2, U606.13
N6_TWLNN: C650.1, R945.2, U616.1, U616.6
N6_TWLNP: C649.1, R944.2, U615.1, U615.6
N6_TWLPN: C648.1, R943.2, U614.1, U614.6
N6_TWLPP: C647.1, R942.2, U613.1, U613.6
N6_TWRNN: C654.1, R949.2, U620.1, U620.6
N6_TWRNP: C653.1, R948.2, U619.1, U619.6
N6_TWRPN: C652.1, R947.2, U618.1, U618.6
N6_TWRPP: C651.1, R946.2, U617.1, U617.6
N6_V3AG_A: Q619.1, R679.1, R680.2, R681.1, R688.1, TP748.1, U605.1
N6_V3AG_A_MCU: R688.2, U201.45
N6_V3AG_B: Q620.1, R686.1, R687.2, R689.1, TP749.1, U605.7
N6_V3AG_B_MCU: R689.2, U201.62
N6_V3AG_S: R681.2, U606.8
N6_V3A_DA: R675.2, R676.1, U605.2
N6_V3A_DB: R682.2, R683.1, U605.6
N6_V3R_A: R677.2, R678.1, R679.2, U605.3
N6_V3R_B: R684.2, R685.1, R686.2, U605.5
N6_V13_CMP: C629.1, R670.2, R671.2, R674.1, U606.5
N6_V13_TEST: D610.3, U201.61
N6_V13_TI: D610.1, R674.2
N6_VLLN: R940.2, R941.1, U614.3, U616.3, U618.3, U620.3
N6_VLLP: R938.2, R939.1, U613.2, U615.2, U617.2, U619.2
N6_VORN: R936.2, R937.1, U611.6, U611.10, U612.6, U612.10
N6_VORP: R934.2, R935.1, R951.1, U611.5, U611.9, U612.5, U612.9
N6_VT: R924.2, R925.1, U609.9, U609.11, U610.9, U610.11
N7_LEDG_A: D705.1, R701.2
N7_LEDR_A: D706.1, R702.2
NRST: C212.1, J201.4, R201.1, U201.7
OSC44_EN: R213.1, TP714.1, U202.3, U205.6, X203.1
OSC48_EN: R212.1, TP713.1, U202.2, X202.1
PROG: TP732.1, U201.2
RAILS_OK_N: R522.2, R532.1, TP721.1, U201.56
RELAY_EN: R646.1, R662.1, TP718.1, U201.44, U608.1
SDATA: R206.2, TP717.1, U301.25
SWCLK: J201.3, U201.49
SWDIO: J201.2, U201.46
USART_RX: J201.8, U201.43
USART_TX: J201.7, U201.42
USB_DN: J101.A7, J101.B7, U101.3, U101.4, U201.58
USB_DP: J101.A6, J101.B6, U101.1, U101.6, U201.59
V3A_MON: C616.1, R246.1, R639.1, R640.1, R661.1
VBUS: C102.1, D102.1, J101.A4/B9, J101.B4/A9, R109.1, TP736.1, TP753.1, U102.6, U502.1
VBUS_SENSE: C103.1, R105.2, R106.1, TP725.1, U201.15
VCCA: C307.1, C440.1, FB302.2, U301.17
VNEG: C410.1, C412.1, C414.1, C416.1, C511.1, C619.1, C627.1, C636.1, C638.1, C656.1, C658.1, C659.2, C660.2, C661.2, C662.2, C663.2, C664.2, C665.2, C666.2, D412.1, R503.1, R936.1, R940.1, TP708.1, U401.4, U401.PAD, U402.4, U402.PAD, U501.6, U603.12, U606.12, U609.12, U610.12, U611.12, U612.12, U613.4, U614.4, U615.4, U616.4, U617.4, U618.4, U619.4, U620.4
VPOS: C409.1, C411.1, C413.1, C415.1, C510.1, C618.1, C626.1, C635.1, C637.1, C655.1, C657.1, C659.1, C660.1, C661.1, C662.1, C663.1, C664.1, C665.1, C666.1, D411.2, R501.1, R647.1, R660.1, R668.1, R672.1, R693.1, R903.2, R905.2, R911.2, R913.2, R916.1, R917.1, R918.1, R919.1, R920.1, R921.1, R922.1, R923.1, R924.1, R942.1, R943.1, R944.1, R945.1, R946.1, R947.1, R948.1, R949.1, TP707.1, U401.2, U401.8, U402.2, U402.8, U501.11, U603.3, U606.3, U609.3, U610.3, U611.3, U612.3, U613.8, U614.8, U615.8, U616.8, U617.8, U618.8, U619.8, U620.8
VREF: C421.1, R431.2, R432.1, R446.2, R447.1, TP709.1, U403.3, U403.5, U404.3, U404.5

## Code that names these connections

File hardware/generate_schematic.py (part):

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    add(replace(base_parts["R951"], row=9002, block=6,
                refs=["R952", "R953"],
                notes="Functional ECO F02: 10 kΩ MCU-side output series resistor"), {
        "R952": [Pin("1", "1", "N6_V3AG_A_BUF_OUT"), Pin("2", "2", "N6_V3AG_A_MCU")],
        "R953": [Pin("1", "1", "N6_V3AG_B_BUF_OUT"), Pin("2", "2", "N6_V3AG_B_MCU")],
    })
    add(replace(base_parts["R680"], row=9003, block=6,
                refs=["R954", "R955"],
                notes="Functional ECO F02: MCU-side pull-up makes an open buffer output fault-high"), {
        "R954": [Pin("1", "1", "3V3M"), Pin("2", "2", "N6_V3AG_A_MCU")],
        "R955": [Pin("1", "1", "3V3M"), Pin("2", "2", "N6_V3AG_B_MCU")],
    })
    add(replace(base_parts["C628"], row=9004, block=6, refs=["C667"],
                notes="Functional ECO F02: 100 nF local bypass at U621 pin 5"), {
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    add(replace(base_parts["D701"], row=9005, block=7,
                refs=["D707", "D708"],
                notes="Functional ECO F04: local J702 LP/RP TVS; verify nonlinear load, grounding and system ESD"), {
        "D707": [Pin("1", "1", "JACK_RP"), Pin("2", "2", "GND")],
        "D708": [Pin("1", "1", "JACK_LP"), Pin("2", "2", "GND")],
    })
    # Functional ECO F05: fit SMD programming headers on the J201 (MCU WCH-Link)
    # and J202 (CPLD) debug pad blocks. Pin order and nets are unchanged.
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    # Functional ECO F06 (v2): layout-driven AGRV2K I/O reassignment (RTL pin constraint
    # change only). The west row is walled by FAM_CLK and its L2-protection via keep-out,
    # so every reassignable signal moves to a side that can escape: the LINK bus, CPLD_IRQ
    # and OSC48_EN to the north row facing U208/U201, OSC44_EN to pin 8 (escapes south).
    cpld_moves = {"10": "27", "11": "26", "12": "28", "14": "29", "2": "31", "3": "8"}
    cpld = {pin.number: pin.net for pin in pins["U202"]}
    expected = {"10": "LINK_MOSI", "11": "LINK_FRAME", "12": "LINK_MISO", "14": "CPLD_IRQ",
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    # Functional ECO F07 (owner decision, 2 October): I2S capture copies. The three DAC-bound
    # N2_*_SRC lines leave pins 18-20 side by side as F.Cu-only 3W routes, so the 330 ohm
    # bit-perfect capture taps cannot branch at the CPLD end. The CPLD now drives dedicated
    # copies of BCLK and SDATA on spare pins 22/23 into R228/R230, which become source series
    # resistors; WS is captured from LRCLK_FB (pin 13), which the notes already define as a copy of
    # LRCLK from its own output register (R229 now taps it). The DAC lines carry no capture stubs.
    # RTL: duplicate the BCLK and SDATA output registers onto pins 22/23 (same edge as 18/20).
    copies = {"22": "N2_CPY_CK", "23": "N2_CPY_SD"}
    taps = {"R228": ("N2_BCLK_SRC", "N2_CPY_CK"), "R229": ("N2_LRCLK_SRC", "LRCLK_FB"),
            "R230": ("N2_SDATA_SRC", "N2_CPY_SD")}
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                     for pin in pins[ref]]
    # Functional ECO F08 (layout-driven CPLD pin rotation, 4 October): east-row IO pins 21-23
    # become N2_CPY_CK / N2_CPY_SD / MCLK_EN (top to bottom: 23 MCLK_EN). The two copies run
    # south-east to R228/R230 and MCLK_EN north-west, so MCLK_EN must take the top pin or it
    # crosses both copies at the pin row. RTL pin constraint change only.
    if (cpld.get("21"), cpld.get("22"), cpld.get("23")) != ("MCLK_EN", "N2_CPY_CK", "N2_CPY_SD"):
        raise ValueError("U202 pins 21-23 changed; re-review CPLD pin ECO F08")
    cpld["21"], cpld["22"], cpld["23"] = "N2_CPY_CK", "N2_CPY_SD", "MCLK_EN"
    pins["U202"] = [Pin(pin.number, pin.name, cpld[pin.number]) for pin in pins["U202"]]
    # Functional ECO F09 (layout-driven, 6 October): CPLD_IRQ moves from north-row pin 29 to west-row
    # pin 3. Pin 29 sits under LINK_MISO's escape via between pins 28 and 30, so no route can leave it;
    # pin 3 (the I/O that carried OSC44_EN before F06) escapes west. RTL pin constraint change only.
    if (cpld.get("29"), cpld.get("3")) != ("CPLD_IRQ", "NC"):
        raise ValueError("U202 pins 29/3 changed; re-review CPLD pin ECO F09")
    cpld["3"], cpld["29"] = "CPLD_IRQ", "NC"
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    # (N6_MCK_RC) to the comparator side of R667 (N6_MCK_CMP), so the probe and its exposed pad no longer
    # sit on the hold node, which now stays a ~3 mm group at D609.
    require("TP747", (("1", "TP", "N6_MCK_RC"),))
    pins["TP747"] = [Pin("1", "TP", "N6_MCK_CMP")]
    return parts, pins, libparts


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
